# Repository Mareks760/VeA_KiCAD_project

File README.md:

# VeA_KiCAD_project
šis readme fails ir paredzēts kursa projektam

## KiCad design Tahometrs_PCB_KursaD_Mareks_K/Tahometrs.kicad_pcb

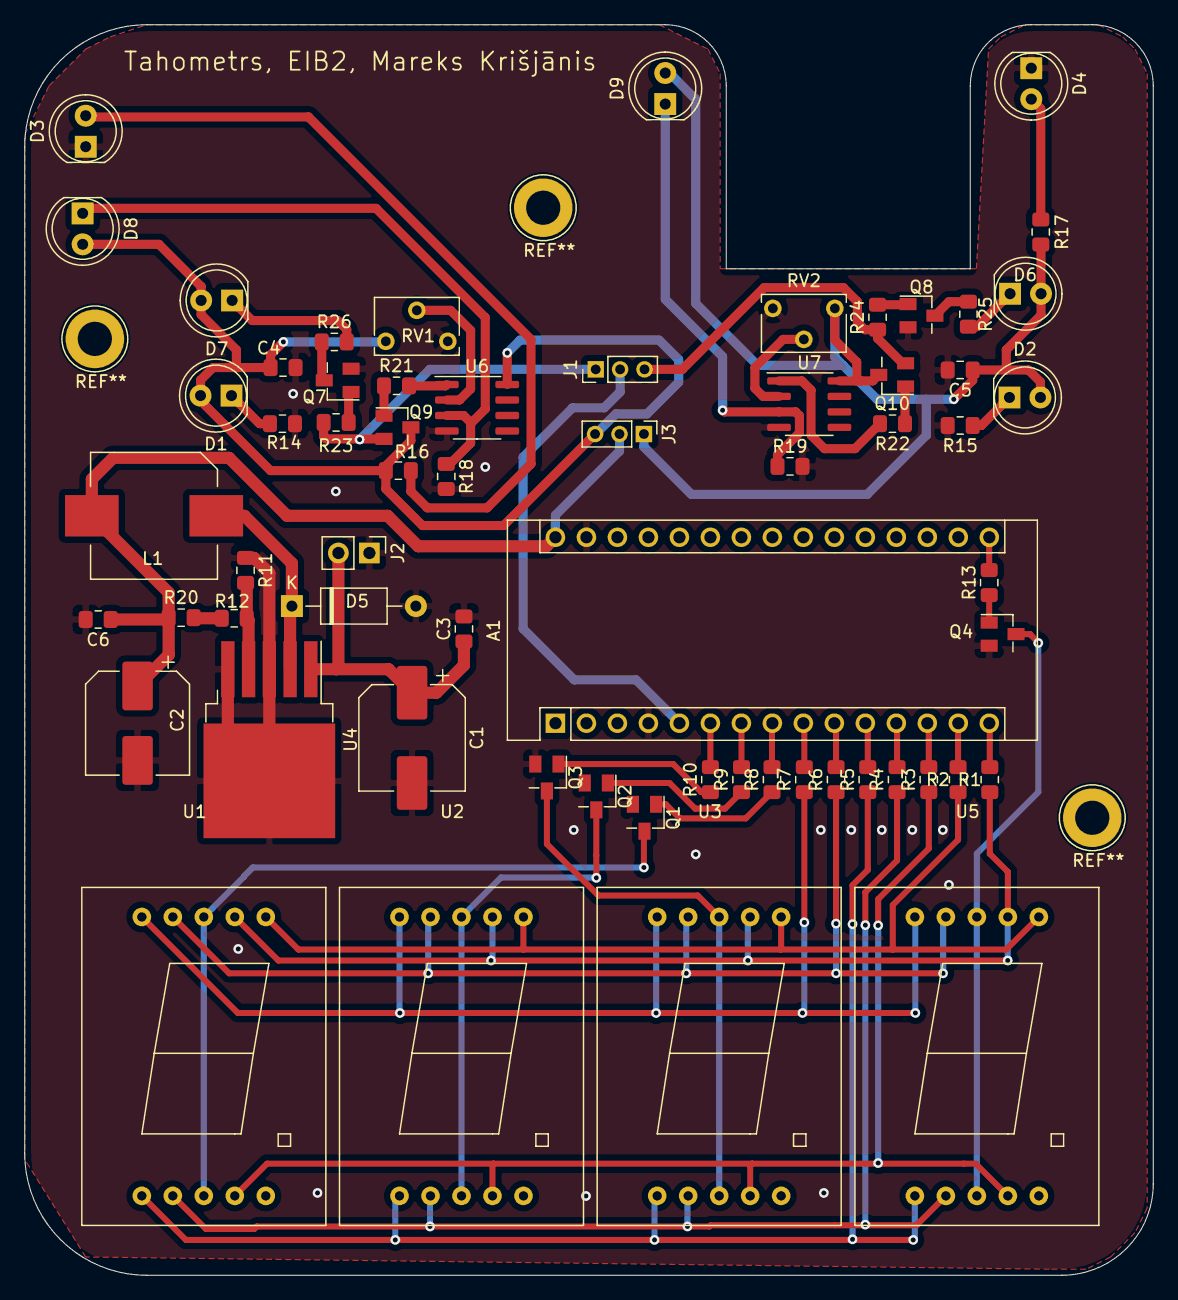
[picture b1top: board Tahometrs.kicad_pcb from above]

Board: 2 copper layers, 92.5 x 102.5 mm, 63 parts (0 on the bottom side), 55 nets.

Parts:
A1: Arduino_Nano_v3.x; Arduino_Nano
C1: 220u; CP_Elec_8x10.5
C2: 220uF; CP_Elec_8x6.2
C3, C6: 100nF; C_0805_2012Metric_Pad1.15x1.40mm_HandSolder
C4, C5: 100 nF; C_0805_2012Metric_Pad1.15x1.40mm_HandSolder
D1, D2: POWER; LED_D5.0mm
D3: IR2; LED_D5.0mm
D4: IR; LED_D5.0mm
D5: D; D_A-405_P10.16mm_Horizontal
D6, D7: PULSE; LED_D5.0mm
D8, D9: D_Photo; LED_D5.0mm
J1, J3: SWITCH; PinHeader_1x03_P2.00mm_Vertical
J2: 4xAA; PinHeader_1x02_P2.54mm_Vertical
L1: 33uH; L_Wuerth_WE-PDF_Handsoldering
Q1, Q2, Q3, Q4, Q7, Q8, Q9, Q10: BC547; SuperSOT-3
R1, R2, R3, R4, R5, R6, R7, R16, R17: 220; R_0805_2012Metric_Pad1.15x1.40mm_HandSolder
R8, R9, R10, R11, R13, R21, R22: 1K; R_0805_2012Metric_Pad1.15x1.40mm_HandSolder
R12: 3K; R_0805_2012Metric_Pad1.15x1.40mm_HandSolder
R14, R15, R25, R26: 560; R_0805_2012Metric_Pad1.15x1.40mm_HandSolder
R18, R19: 27K; R_0805_2012Metric_Pad1.15x1.40mm_HandSolder
R20: 56; R_0805_2012Metric_Pad1.15x1.40mm_HandSolder
R23, R24: 470; R_0805_2012Metric_Pad1.15x1.40mm_HandSolder
RV1, RV2: 10K; Potentiometer_Bourns_3266W_Vertical
U1, U2, U3, U5: SM420561N; SM420806N
U4: LM2596S-ADJ; TO-263-5_TabPin3
U6, U7: LM393; SOIC-8_3.9x4.9mm_P1.27mm

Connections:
5V: A1.30, C2.1, C6.1, J3.2, L1.2, R20.1
=: C4.1, D1.2, D7.2, D8.2, J3.3, Q9.3, R16.1, RV1.1, U6.8
A: A1.15, R1.2
B: A1.14, R2.2
C: A1.13, R3.2
D: A1.12, R4.2
D1: A1.8, R8.2
D2: A1.7, R9.2
D3: A1.6, R10.2
D4: A1.16, R13.2
D_out: J1.3, Q10.2, R24.1
D_out2: J1.1, Q9.2, R23.1
E: A1.11, R5.2
F: A1.10, R6.2
G: A1.9, R7.2
GNDREF: A1.4, A1.29, C1.2, C2.2, C3.2, C4.2, C5.2, C6.2, D3.1, D4.1, D5.2, J2.1, Q1.2, Q2.2, Q3.2, Q4.2, Q7.2, Q8.2, R11.1, R14.2, R15.2, R18.2, R19.2, RV1.3, RV2.3, U4.3, U4.5, U6.4, U7.4
unnamed: A1.5, J1.2
unnamed: C1.1, C3.1, J2.2, U4.1
unnamed: D1.1, R14.1
unnamed: D2.1, R15.1
unnamed: D3.2, R16.2
unnamed: D4.2, R17.2
unnamed: D5.1, L1.1, U4.2
unnamed: D6.1, R25.2
unnamed: D7.1, R26.2
unnamed: D8.1, R18.1, U6.3
unnamed: D9.1, R19.1, U7.3
unnamed: Q1.1, R8.1
unnamed: Q1.3, U1.3, U1.8
unnamed: Q2.1, R9.1
unnamed: Q2.3, U2.3, U2.8
unnamed: Q3.1, R10.1
unnamed: Q3.3, U3.3, U3.8
unnamed: Q4.1, R13.1
unnamed: Q4.3, U5.3, U5.8
unnamed: Q7.1, R23.2
unnamed: Q7.3, R26.1
unnamed: Q8.1, R24.2
unnamed: Q8.3, R25.1
unnamed: Q9.1, R21.1
unnamed: Q10.1, R22.1
unnamed: R1.1, U1.7, U2.7, U3.7, U5.7
unnamed: R2.1, U1.6, U2.6, U3.6, U5.6
unnamed: R3.1, U1.4, U2.4, U3.4, U5.4
unnamed: R4.1, U1.2, U2.2, U3.2, U5.2
unnamed: R5.1, U1.1, U2.1, U3.1, U5.1
unnamed: R6.1, U1.9, U2.9, U3.9, U5.9
unnamed: R7.1, U1.10, U2.10, U3.10, U5.10
unnamed: R11.2, R12.2, U4.4
unnamed: R12.1, R20.2
unnamed: R21.2, U6.1
unnamed: R22.2, U7.1
unnamed: RV1.2, U6.2
unnamed: RV2.2, U7.2
x: C5.1, D2.2, D6.2, D9.2, J3.1, Q10.3, R17.1, RV2.1, U7.8

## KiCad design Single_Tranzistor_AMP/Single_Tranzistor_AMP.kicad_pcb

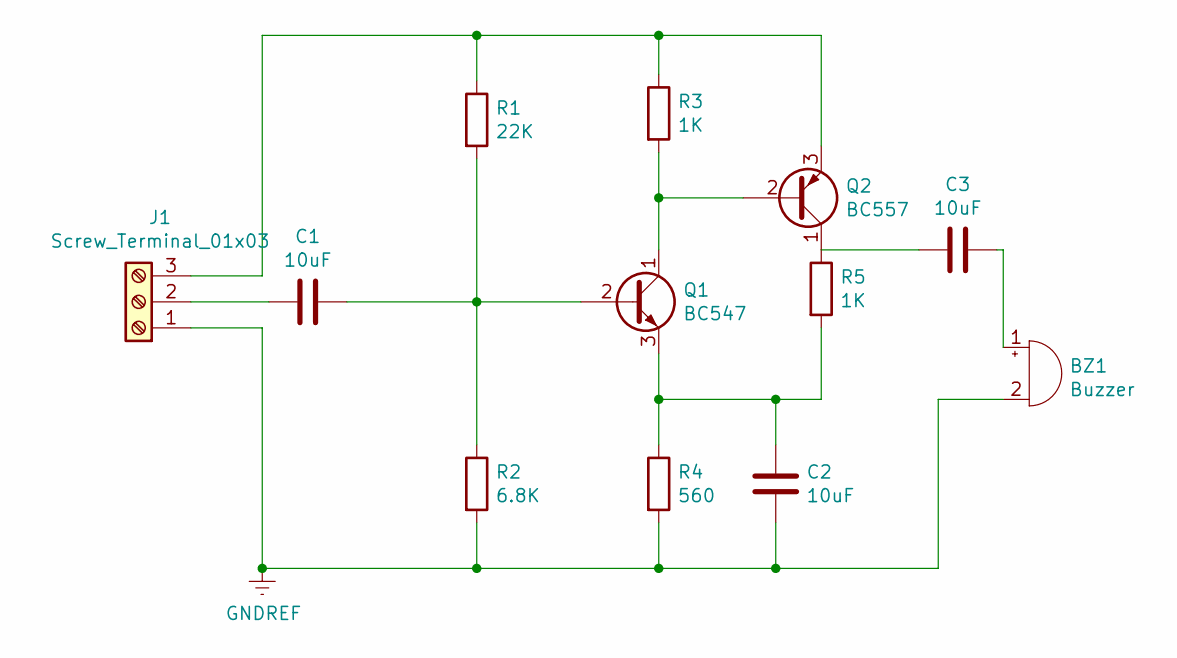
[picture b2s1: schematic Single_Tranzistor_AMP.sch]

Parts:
BZ1: Buzzer; Buzzer_D14mm_H7mm_P10mm
C1, C2, C3: 10uF; R_0805_2012Metric_Pad1.15x1.40mm_HandSolder
J1: Screw_Terminal_01x03; TerminalBlock_4Ucon_1x03_P3.50mm_Vertical
Q1: BC547; TO-92_Inline
Q2: BC557; TO-92_Inline
R1: 22K; R_0805_2012Metric_Pad1.15x1.40mm_HandSolder
R2: 6.8K; R_0805_2012Metric_Pad1.15x1.40mm_HandSolder
R3, R5: 1K; R_0805_2012Metric_Pad1.15x1.40mm_HandSolder
R4: 560; R_0805_2012Metric_Pad1.15x1.40mm_HandSolder

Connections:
GNDREF: BZ1.2 (+), C2.2, J1.1, R2.2, R4.2
unnamed: BZ1.1 (-), C3.2
unnamed: C1.1, J1.2
unnamed: C1.2, Q1.2 (B), R1.2, R2.1
unnamed: C2.1, Q1.3 (E), R4.1, R5.2
unnamed: C3.1, Q2.1 (C), R5.1
unnamed: J1.3, Q2.3 (E), R1.1, R3.1
unnamed: Q1.1 (C), Q2.2 (B), R3.2

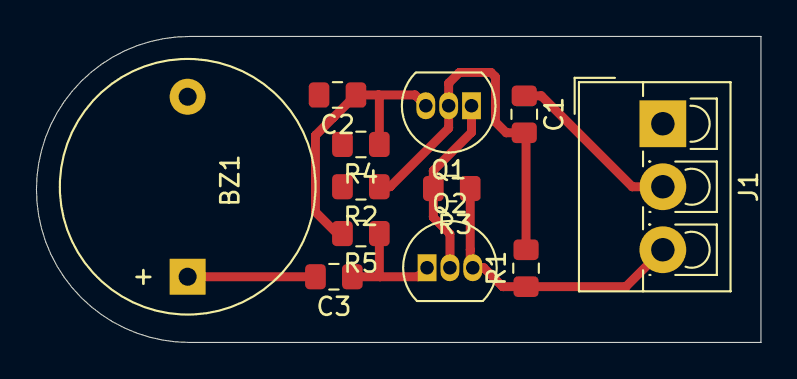
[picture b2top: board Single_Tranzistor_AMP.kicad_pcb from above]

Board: 2 copper layers, 40.2 x 17.0 mm, 12 parts (0 on the bottom side), 8 nets.

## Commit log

2020-09-22 add link to the OpenTechSchool course material
2020-10-07 MUlti Vib mājasdarbs
2020-10-09 2_md_Power_supply
2020-10-14 3 majasdarbs par pastiprinatajiem
2020-10-22 stundas uzd par batterijam
2020-10-22 4 md par baterijām un to lodlaukumiem
2020-11-01 majas darbs par single tranzistor PCBnew settings
2020-11-17 6 nodarbibas majasdarbs
2020-12-03 majasdarbs par celinu trasesanu
2021-01-25 Kursa_darbs_Mareks_K
